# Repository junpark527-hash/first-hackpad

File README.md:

## My first every Hackpad!

A custom numpad style macropad, built for the NASA x Hack Club Stardance Challenge.

# About

I faced many difficulties, challenges, and learning curves throughout this whole process, but in the end, I am extremely glad that I took the time to learn all these new skills. I had to redo my entire idea that I had planned from the beginning because of issues I faced with wiring and pins, but it was quite fun tinkering with these new software programs, and I am happy with the results. My build consists of an OLED screen, an encoder, some keys, and a case.

# Features:
QMK firmware
a 3-part case (3D printed)
128x32 OLED Display
EC11 Rotary encoder for volume and brightness 
8 keys/switches
8 SK6812MINI-E LEDs
4 M2 heatset inserts and screws

# CAD Model

This case has 3 separate parts: one for the bottom of the case, one for the top half, and one for the bottom half of the top. The top half consists of the cutouts for my OLED and encoder, and the other half has the key switch cutout. I am planning on assembling the case together using M2-Heatset inserts and screws on each corner. It also has 4 small raised pillars in the bottom of the case for my pcb to rest on. Additionally, I made a cutout for the USB on the XIAO.

# Schematic
This is my Schematic: 

# PCB
This is my PCB: 

# Firmware
I have a total of 8 keys on this hackpad with a rotary encoder. Based on the click of one of the keys, I can change the function of the encoder from brightness adjustment to volume adjustment. The other keys will be used for other functions like copy and paste, media controls, and opening a new file explorer tab or task manager.

# BOM
This is everything that should be needed to make this hackpad: 

* 8x Cherry MX-style Switches
* 8x White Blank DSA Keycaps
* 4x M3x5x4mm Heatset inserts
* 4x M3x16mm Screws
* 8x 1N4148 Diodes
* 8x SK6812MINI-E LEDs
* 1x 0.91" 128x32 OLED Display
* 1x EC11 Rotary Encoder
* 1x XIAO RP2040
* 1x Case (3 printed parts)
* I will also be needing a soldering iron!

See [JOURNAL.md](JOURNAL.md) for progress notes.

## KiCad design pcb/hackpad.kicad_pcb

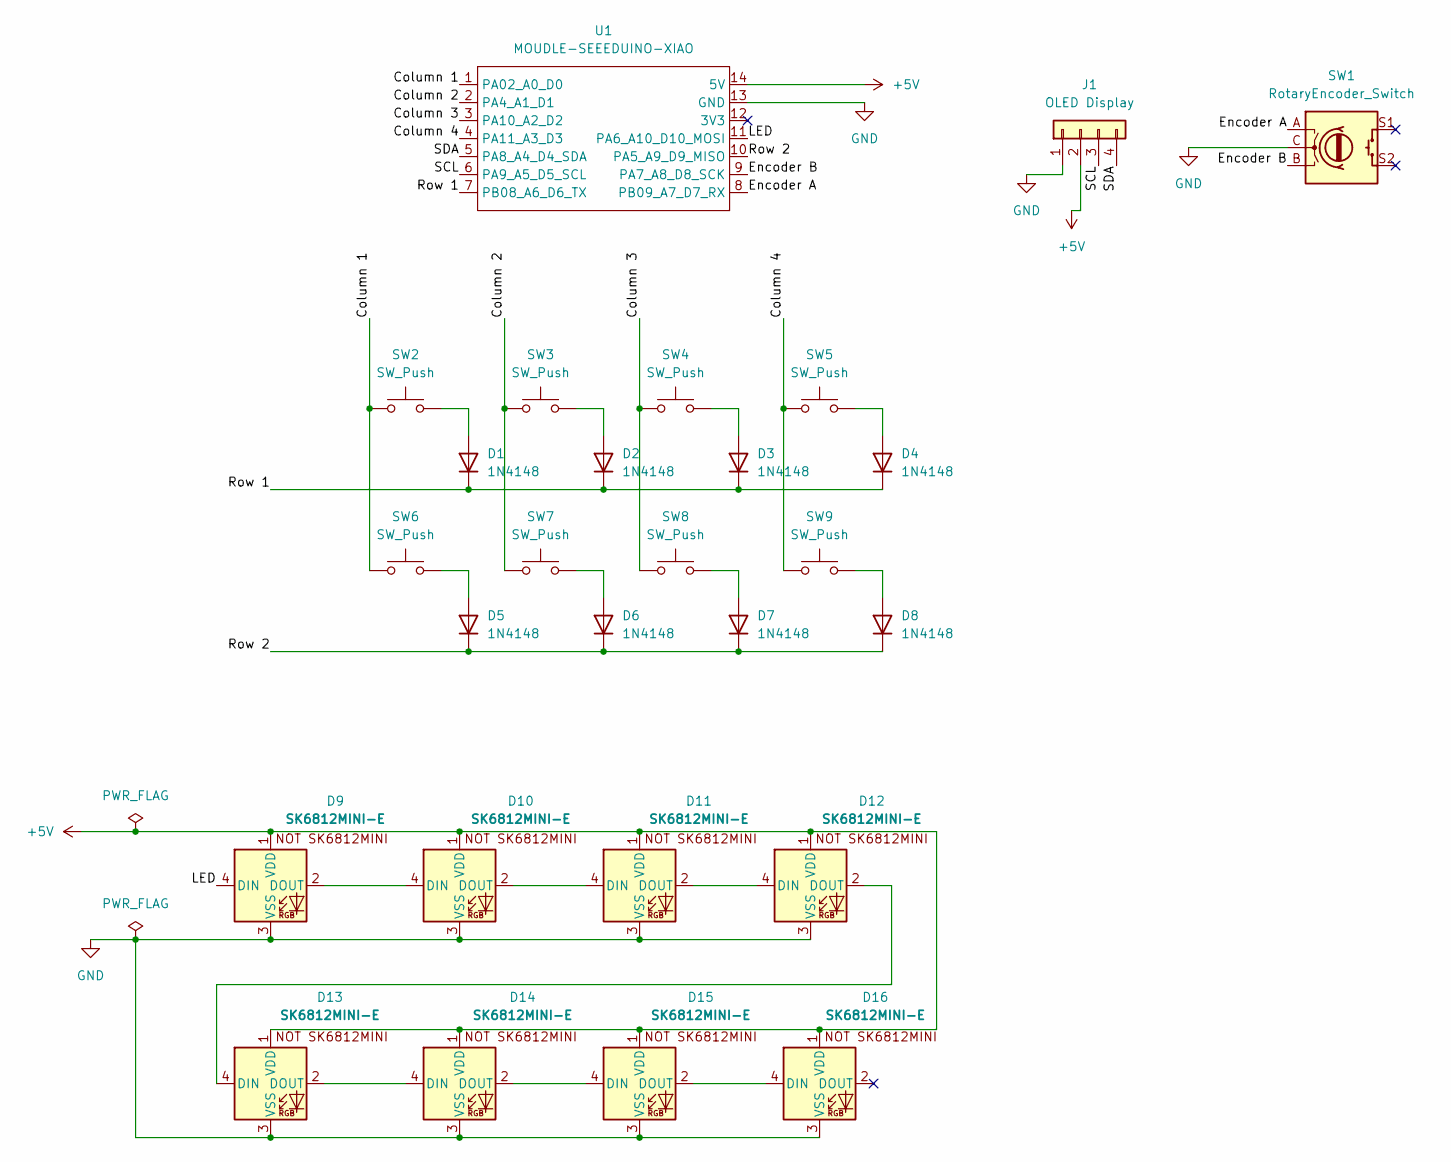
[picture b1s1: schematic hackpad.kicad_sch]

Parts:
D1, D2, D3, D4, D5, D6, D7, D8: 1N4148; D_DO-35_SOD27_P7.62mm_Horizontal
D9, D10, D11, D12, D13, D14, D15, D16: SK6812MINI-E; SK6812MINI-E_fixed
J1: OLED Display; SSD1306-0.91-OLED-4pin-128x32
SW1: RotaryEncoder_Switch; RotaryEncoder_Alps_EC11E-Switch_Vertical_H20mm
SW2, SW3, SW4, SW5, SW6, SW7, SW8, SW9: SW_Push; SW_Cherry_MX_1.00u_PCB
U1: MOUDLE-SEEEDUINO-XIAO; XIAO-Generic-Hybrid-14P-2.54-21X17.8MM

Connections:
+5V: D9.1 (VDD), D10.1 (VDD), D11.1 (VDD), D12.1 (VDD), D13.1 (VDD), D14.1 (VDD), D15.1 (VDD), D16.1 (VDD), J1.2, U1.14 (5V)
/Column 1: SW2.1, SW6.1, U1.1 (PA02_A0_D0)
/Column 2: SW3.1, SW7.1, U1.2 (PA4_A1_D1)
/Column 3: SW4.1, SW8.1, U1.3 (PA10_A2_D2)
/Column 4: SW5.1, SW9.1, U1.4 (PA11_A3_D3)
/Encoder A: SW1.A, U1.8 (PB09_A7_D7_RX)
/Encoder B: SW1.B, U1.9 (PA7_A8_D8_SCK)
/LED: D9.4 (DIN), U1.11 (PA6_A10_D10_MOSI)
/Row 1: D1.1 (K), D2.1 (K), D3.1 (K), D4.1 (K), U1.7 (PB08_A6_D6_TX)
/Row 2: D5.1 (K), D6.1 (K), D7.1 (K), D8.1 (K), U1.10 (PA5_A9_D9_MISO)
/SCL: J1.3, U1.6 (PA9_A5_D5_SCL)
/SDA: J1.4, U1.5 (PA8_A4_D4_SDA)
GND: D9.3 (VSS), D10.3 (VSS), D11.3 (VSS), D12.3 (VSS), D13.3 (VSS), D14.3 (VSS), D15.3 (VSS), D16.3 (VSS), J1.1, SW1.C, U1.13 (GND)
unnamed: D1.2 (A), SW2.2
unnamed: D2.2 (A), SW3.2
unnamed: D3.2 (A), SW4.2
unnamed: D4.2 (A), SW5.2
unnamed: D5.2 (A), SW6.2
unnamed: D6.2 (A), SW7.2
unnamed: D7.2 (A), SW8.2
unnamed: D8.2 (A), SW9.2
unnamed: D9.2 (DOUT), D10.4 (DIN)
unnamed: D10.2 (DOUT), D11.4 (DIN)
unnamed: D11.2 (DOUT), D12.4 (DIN)
unnamed: D12.2 (DOUT), D13.4 (DIN)
unnamed: D13.2 (DOUT), D14.4 (DIN)
unnamed: D14.2 (DOUT), D15.4 (DIN)
unnamed: D15.2 (DOUT), D16.4 (DIN)

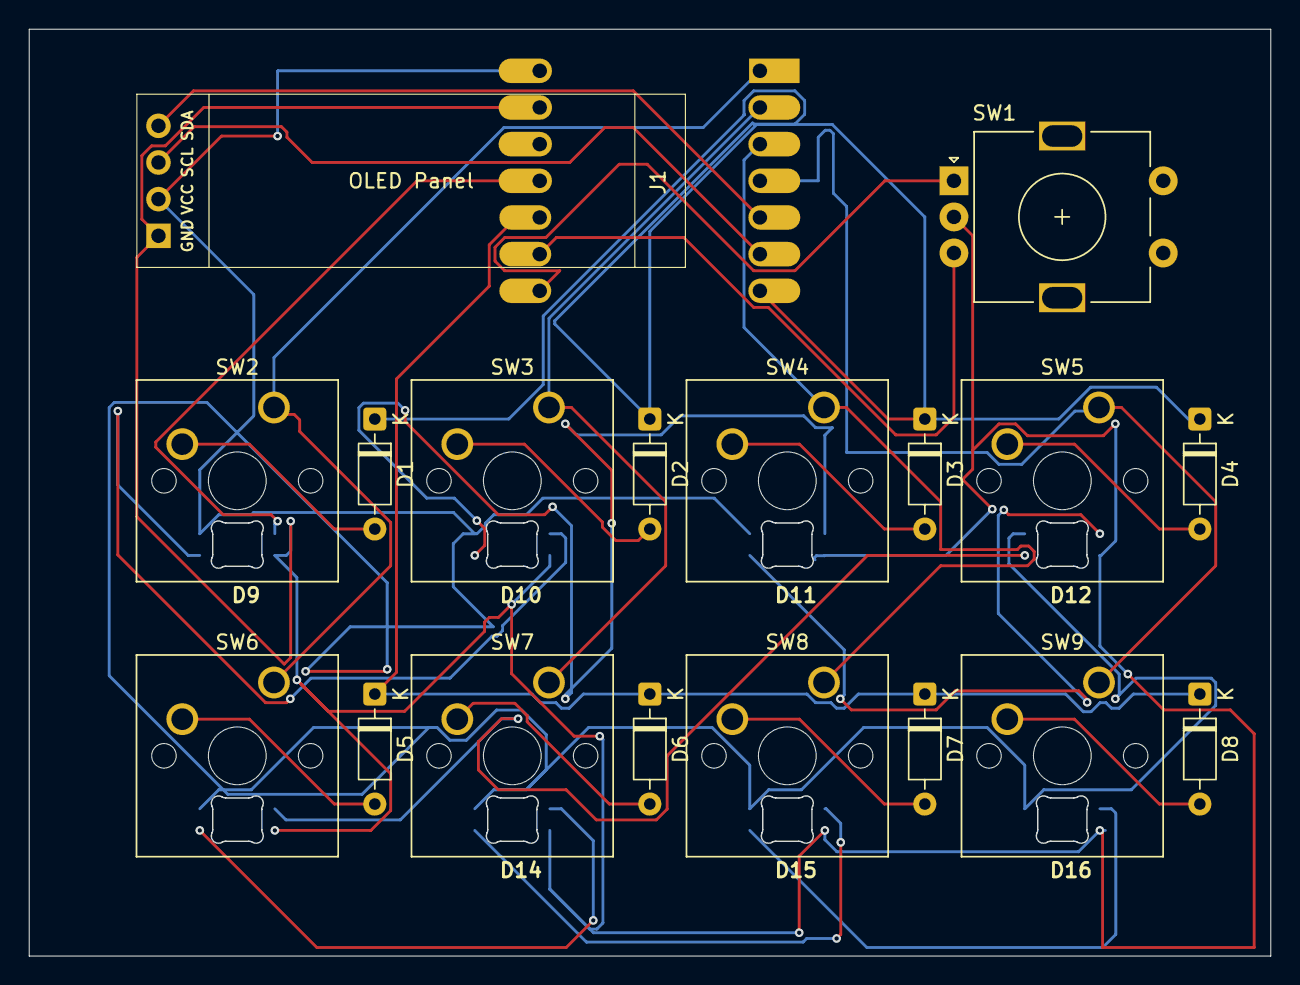
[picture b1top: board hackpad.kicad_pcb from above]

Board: 2 copper layers, 86.0 x 64.2 mm, 27 parts (1 on the bottom side), 28 nets.
